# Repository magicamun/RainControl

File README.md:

# RainControl
Füllstandsmessung einer Zisterne, (Über-)steuerung des Schwimmerschalters der Regenwasserpumpe in Abhängigkeit des Füllstands. 
Messung Strom, Verbrauch der Pumpe, Ableitung an/aus. Anbindung an einen MQTT-Broker zur Werteerfassung und Steuerung

Das Projekt basiert auf der Arbeit aus diesem Repo:

https://github.com/Eisbaeeer/Arduino.Ethernet.Zisterne

Der Nano war aber am Limit was den Speicherplatz angeht und selbst kleinste Optimierungen führten zu zu großen Images oder liefen im Betrieb instabil,
daher habe ich das Projekt auf anderer Hardware aufgesetzt. Zugegeben - das ist jetzt deutlich teurer aber macht so auch mehr Spaß (finde ich).
Ich benötige mangels stabilem WLAN im Technikraum Ethernet - daher das Shield.

Hardware:
  [Arduino MKR Zero](https://store.arduino.cc/collections/mkr-family/products/arduino-mkr-zero-i2s-bus-sd-for-sound-music-digital-audio-data) 
  
  [MKR Ethernet-Shield](https://store.arduino.cc/collections/mkr-family/products/arduino-mkr-eth-shield) - Zur Anbindung an eine Hausatomation, bzw. an einen MQTT-Broker (IOBroker)
  
  Pegelsonde zur Messung des Füllstands mittels Druck - Voraussetzung zur korrekten Füllstandsermittlung ist ein Höhensymmetrisches Volumen (aufrecht stehender Zylinder, Quader), Liegende Zylinderformen sind nicht geeignet. Z.B. so eine hier:
  
  [Füllstandssensor Pegelsensor Drucksensor Wasserstandsensor 4-20mA 0-5m DE](https://www.ebay.de/itm/177255784278?chn=ps&_ul=DE&_trkparms=ispr%3D1&amdata=enc%3A10OVVLQ0TSaWD2zqcidwIyQ23&norover=1&mkevt=1&mkrid=707-134425-41852-0&mkcid=2&mkscid=101&itemid=177255784278&targetid=2381626844604&device=c&mktype=pla&googleloc=9113680&poi=&campaignid=21674357977&mkgroupid=167855164998&rlsatarget=pla-2381626844604&abcId=10011854&merchantid=5588616187&gad_source=1&gad_campaignid=21674357977&gbraid=0AAAAAD_G4xa4yudELXTO8UWhM-5WBP-aM&gclid=CjwKCAjwkvbEBhApEiwAKUz6-0uRbySDVDx1-_a3FiXcqrZ4Tvtlft7q06sarqXWDDbmrJJIIFPkExoCPcMQAvD_BwE)
  
  [Stromsensor SCT013 - 5A, 1V](https://www.amazon.de/HUABAN-Nicht-invasiver-Split-Core-Stromwandlersensor/dp/B089FNQ5GX?th=1)

  [Steckernetzteil 24V DC](https://www.conrad.de/de/p/dehner-elektronik-saw-30-240-1000g-steckernetzteil-festspannung-24-v-dc-1000-ma-24-w-1549855.html)

Bauteile für die Schaltung, Platine
  
  Controller
  - [Spannungswandler TSR-1 2433 (Wandlung Eingangsspannung 24V auf 3,3V](https://www.conrad.de/de/p/tracopower-tsr-1-2433-dc-dc-wandler-print-24-v-dc-3-3-v-dc-1-a-75-w-anzahl-ausgaenge-1-x-inhalt-1-st-156671.html) zur Versorgung der Schaltung mit 3,3V
  - [Strom/Spannungswandler](https://de.aliexpress.com/item/1005001604138590.html) zur Wandlung des Stroms der Sonde in Spannung inkl. Kalibrierung von 0-Punkt und Maximum
  - [Relais Finder 36.11 Schaltspannung 3V](https://www.conrad.de/de/p/finder-36-11-9-003-4011-printrelais-3-v-dc-10-a-1-wechsler-1-st-3323202.html)
  - [Steckerleisten 14 polig](https://www.conrad.de/de/p/econ-connect-buchsenleiste-standard-anzahl-reihen-1-polzahl-je-reihe-14-blg1x14-1-st-1492306.html)
  - [Transistor BC337](https://www.conrad.de/de/p/diotec-transistor-bjt-diskret-bc337-25-to-92-anzahl-kanaele-1-npn-155900.html) zur Schaltung von Relais und LED
  - D1 [Diode (1N 4148)](https://www.conrad.de/de/p/diotec-ultraschnelle-si-diode-1n4148-sod-27-75-v-150-ma-162280.html)
  - R1 [1x Widerstand 330 Ohm](https://www.conrad.de/de/p/yageo-cfr25j330rh-cfr-25jt-52-330r-kohleschicht-widerstand-330-axial-bedrahtet-0207-0-25-w-5-1-st-1417730.html)
  - R2, R3 [2x Widerstand 10k Ohm](https://www.conrad.de/de/p/yageo-cfr25j10kh-cfr-25jt-52-10k-kohleschicht-widerstand-10-k-axial-bedrahtet-0207-0-25-w-5-1-st-1417697.html)
  - [10uF Elko](https://www.conrad.de/de/p/frolyt-e-rf3058-elektrolyt-kondensator-radial-bedrahtet-2-5-mm-10-f-16-v-20-o-x-l-5-mm-x-12-mm-1-st-3046377.html)
  - 3 x [Schraubklemmblock 2 polig](https://www.conrad.de/de/p/deca-1216197-schraubklemmblock-1-50-mm-polzahl-3-blau-1-st-1216197.html) (Sonde Zisterne, Spannungsversorgung 24V, Stromsensor SCT 013)
  - 1 x [Schraubklemmblock 3-polig](https://www.conrad.de/de/p/deca-1282826-schraubklemmblock-1-50-mm-polzahl-2-blau-1-st-1282826.html) (Umschaltung Regenwasserpumpe, Übersteuerung Schwimmerschaltung - ACHTUNG - 230V)
  
  Displaypanel
  - R1 [1x Widerstand 390 Ohm](https://www.conrad.de/de/p/yageo-mf0207f390rh-mf0207fte52-390r-metallschicht-widerstand-390-axial-bedrahtet-0207-0-6-w-1-1-st-1417596.html)
  - [LED - Rot, 3mm](https://www.conrad.de/de/p/quadrios-2111o155-led-bedrahtet-rot-rund-3-mm-700-mcd-30-20-ma-2-v-2583896.html)
  - [2 Taster (Reset und Mode)](https://www.conrad.de/de/p/weltron-t604-t604-drucktaster-24-v-dc-0-05-a-1-x-aus-ein-tastend-l-x-b-x-h-6-x-6-x-9-5-mm-1-st-700479.html)
  Display
  - [2,42" 128X64-OLED-Anzeigemodul SPI - 2.42 Zoll OLED Bildschirm kompatibel mit Arduino UNO R3 - Weiße Schrift OLED :](https://www.az-delivery.de/products/oled-2-4-white?variant=44762703986955&utm_source=google&utm_medium=cpc&utm_campaign=16964979024&utm_content=166733588295&utm_term=&gad_source=1&gbraid=0AAAAADBFYGXj7s2C_h3TASz0DupxomgUw&gclid=EAIaIQobChMI-YCAy9LmjAMVH5CDBx0H8zKnEAQYAyABEgLpafD_BwE)

  Zur Verbindung von Controllerplatine mit der Displayplatine:
  
  2 x [Wannenstecker 8polig](https://www.conrad.de/de/p/bkl-electronic-10120552-stiftleiste-ohne-auswurfhebel-rastermass-2-54-mm-polzahl-gesamt-8-anzahl-reihen-2-1-st-741552.html?hk=SEM&WT.mc_id=google_pla&utm_source=google&utm_medium=cpc&utm_campaign=DE+-+PMAX+-+Nonbrand+-+Learning&utm_id=20402606569&gad_source=1&gad_campaignid=20392975386&gbraid=0AAAAAD1-3H7MMs8aUj1DVyRg7EW9yTu3l&gclid=CjwKCAjwkvbEBhApEiwAKUz6--gW1qskdMad7NtT7sFPgiCQdok8dU4I2qlc02XzfEHAeNsRRdUxyhoCCR4QAvD_BwE)
  
  2 x [Pfostensteckverbinder mit Zugentlastung](https://www.conrad.de/de/p/tru-components-1580952-pfosten-steckverbinder-mit-zugentlastung-rastermass-2-54-mm-polzahl-gesamt-8-anzahl-reihen-2-1-1580952.html?hk=SEM&WT.mc_id=google_pla&utm_source=google&utm_medium=cpc&utm_campaign=DE+-+PMAX+-+Nonbrand+-+Learning&utm_id=20402606569&gad_source=1&gad_campaignid=20392975386&gbraid=0AAAAAD1-3H7MMs8aUj1DVyRg7EW9yTu3l&gclid=CjwKCAjwkvbEBhApEiwAKUz6--gW1qskdMad7NtT7sFPgiCQdok8dU4I2qlc02XzfEHAeNsRRdUxyhoCCR4QAvD_BwE)
  
  1 x [Flachbandkabel 8 polig](https://www.conrad.de/de/p/econ-connect-28awg8gr-flachbandkabel-rastermass-1-27-mm-8-x-0-08-mm-grau-30-50-m-1656444.html)

  Sonstiges Material:
  - Bopla Gehäuse](https://www.conrad.de/de/p/bopla-euromas-m-231-02231000-industrie-gehaeuse-160-x-80-x-85-polycarbonat-lichtgrau-ral-7035-1-st-531785.html?hk=SEM&WT.mc_id=google_pla&utm_source=google&utm_medium=cpc&utm_campaign=DE+-+PMAX+-+Nonbrand+-+Learning&utm_id=20402606569&gad_source=1&gad_campaignid=20392975386&gbraid=0AAAAAD1-3H4SrPRlOXxmb1LvpAf_dMIkF&gclid=Cj0KCQjwnovFBhDnARIsAO4V7mCVA2QiVP_xAGgSJM6bk3FJjILpeI0nTC0QpojrSp9-wGSnNphEn0QaArxKEALw_wcB)
  - [Passende Einbaubuchse für das Netzteil](https://www.conrad.de/de/p/cliff-scd-026-niedervolt-steckverbinder-buchse-einbau-vertikal-5-5-mm-2-1-mm-1-st-735640.html)
  - [Einbaubuchse für Klinkenstecker vom SCT013](https://www.conrad.de/de/p/tru-components-718574-klinken-steckverbinder-3-5-mm-buchse-einbau-vertikal-polzahl-3-stereo-schwarz-1-st-1564526.html)
    
Das Platinenlyout wurde mit KiCad in 2 Projekten erstellt - eines für das Display, eines für den Controller.

Funktionsweise technisch:

Füllstandsmessung:
  Die Sonde wird mit 24V betrieben und da bietet sich ein Netzteil handelsüblich an und eine Spannungswandlung (TSR-1 2433) von den 24V DC auf 3,3V für den Rest der Schaltung (Arduino MKR Zero, Relais, Display).
  Die Sonde liefert einen Strom in Abhängigkeit vom Druck (Füllstandshöhe). Der Wandler macht aus dem Strom eine Ausgangsspannung von 0 bis Vmax (3,3V).
  Diese Spannung wird am A0 (AnalogInput 0) des Arduino erfasst und in einen Füllstand umgerechnet - der Füllstand (Volumen) ist proportional zum gemessenen Wert an A0.
  Voraussetzung ist ein Behälter, dessen Füllstand (Volumen) sich linear proportional zum Druck verhält (Senkrechter Zylinder).
  
  Der Wandler für den Messwert an A0 muss vor Inbetriebnahme des Systems kalibiriert werden.
  ACHTUNG: Die Kalibrierung muss im ersten Schritt grob ohne angeschlossenen Arduino erfolgen um Beschädigungen durch Überspannung am Eingang des Arduino zu vermeiden.
  -> Siehe Kalibrierung und Inbetriebnahme.
  
  In Abhängigkeit von der gemessenen Füllhöhe und zwei einzustellenden Werten (LimitLow, LimitHigh) schaltet der Arduino das Relais sowie eine LED über PIN D14 an oder aus.
  Damit bei unterem Schwellwert / Minimum nicht sofort bei erneutem überschreiten (Nachlauf Regen) wieder zurück geschaltet wird, gibt es einen weiteren Wert (Oberer Schwellwert),
  der erreicht werden muss, damkt zurück auf Zisterne geschaltet wird.

Strom, Pumpe an oder aus:
  Über den Stromsensor SCT013 kann der Zustand der Pumpe (Regenwassernutzung) abgefragt werden, ohne in die Anlage eingreifen zu müssen.
  Dazu wird der Stromsensor unter der Beachtung der Stromflussrichtung um die Phase (nur die Phase) zur Pumpe gelegt.
  Am Ausgang des Sensors wird über Induktion eine Wechselspannung abgegeben. Dabei sind die Werte des Sensors zur korrekten Berechnung des Stroms und der Leistung in der Software einzustellen.
   Wichtig ist eine korrekte Dimensionierung des Sensors - es gibt unterschiedliche Typen. Für eine möglichst feine Auflösung ist der Messbereich (Ampere) des Sensors möglichst klein zu wählen, 
   aber groß genug, dass bei Vollast der Pumpe der Wert der Leistung ausreicht. Der hier benutzte Sensor misst bis 5A -> 1,1kw. Meine Pumpe hat 800 Watt Leistungsaufnahme.
   Gleichzeitig soll der Sensor möglichst große Spannungswerte am Ausgang produzieren, damit die Auflösung des Wertes möglichst fein/genau ist.
   Es gibt die Sensoren mit 0,33V und 1V Ausgangsspannung -> ich nutze hier 1V. Da die Spannung eine Wechselspannung ist, wird über den Spannungsteiler am Sensor die Wechselspannung um +1,65V angehoben.
   Der analoge Wert an A1 wird in einen Wert für den Stromverbrauch umgerechnt. Dazu ist es wichtig, den Messbereich des Sensors, die Ausgangsspannung des Sensors und den Referenzwert am Arduino (Zero 3,3V)
   zu kennen und in der Software einzustellen.

Am Pin D13 ist ein Taster von der Displayplatine angeschlossen, mit dem der Betriebsmodus der Steuerung manuell gesetzt werden kann:
  - Auto - Der Arduino übernimmt die Ventilsteuerung (Relais und Ansteuerung Schwimmerschalter der Pumpe) in abhängigkeit des Füllstandes
  -   Füllstand < LimitLow -> Relais auf "Hauswasser"
  -   Füllstand > LimitHigh -> Relais auf "Zisterne"
  -   Wenn der Füllstand kleiner als LimitLow war und immernoch kleiner als LimitHigh ist -> Ventil auf Hauswasser
  - Manuell Zisterne -> Relais auf "Zisterne"
  - Manuell Hauswasser -> Relais auf "Hauswasser"

  Per Tasterdruck wird zyklisch durch die Betriuebsmodi geschaltet, wobei die tatsächliche Umschaltung erst nach 10Sekunden ohne erneute Tasterbetätigung erfolgt

Das Display zeigt Datum, Uhrzeit, Füllstand und Betriebsmodus an

Mit dem an RST angeschlossenen Taster lässt sich der Controller resetten.

Ventilsteuerung generell:
Der Controller misst den Füllstand und (kann) in Abhängigkeit davon einen Schwimmerschalter für handelsübliche Zisternenpumpen ersetzen. Dazu ist die Steuerung der Pumpe auf "Automatik" zu stellen
und statt des Schwimmerschalters ein 230V - Kabel vom Anschluss des Schwimmerschalters zum Controller (3 - polige Klemme) zu führen.
Am Schraubklemmenblock 3 polig ist in jedem der mittlere Anschluss zu belegen und dann entweder NO (Normally open) oder NC (normally connected) - sonst schaltet am Ventil der Regenwasserpump nichts.

Funktionsweise Software:

Sämtliche Systemzustände werden bei Veränderung alle Sekunde an einen MQTT-Broker gesendet, spätestens alle 30 Sekunden auch unverändert. Das System führt folgende Werte:

- Booted     -> Boot-Zeitpunkt
- Timestamp  (Datum, Uhrzeit)
- Uptime     -> Zeit seit l. Boot/Neustart
- Mode       (0 = Zisterne, 1 = Hauswasser, 2 = Auto) -> Betriebsmodus
- Modus      -> Modus als Text
- Valve      (0 = Zisterne, 1 = Hauswasser) -> Ventilstellung
- Ventil     -> Ventilstellung als Text ("Zisterne", "Hauswasser")
- Reason     -> Grund für Ventilstellung (0 = "Manuell", 1 = "Zisterne voll", 2 = "Zisterne leer")
- Reasontext -> Reason als Text
- AnalogMin  -> Mindestwert, den die Sonde liefern muss, damit Sonde als vorhanden erkannt wird
- AnalogMax  -> Maximaler analoger Wert an A0 für volle Zisterne
- Analog     (0-1023) -> Analoger Messwert der Pegelsonde (0-1023)
- Liter      -> Füllung in Liter
- Prozent    -> Füllstand in %
- LimitLow   -> Unterer Schwellwert in Liter
- LimitHigh  -> Oberer Schwellwert in Liter
- LiterMin   -> Restfüllstand bei "leer" - unterer Grenzwert -> AnalogMin.
- LiterMax   -> maximales Füllvolumen wird benötigt zur Umrechnung des analogen Wertes in Liter (Analog = LiterMax / AnalogMax)
- StatusSonde-> Ist eine Sonde korrekt angeschlosen (Wenn der Analoge Wert unter einem Minimum liegt, dann ist davon auszugehen, dass die Sonde nicht korrekt angeschlossen ist
- HyaRain    -> Pumpe läuft (ON), oder nicht (OFF)
- Current    -> Stromverbrauch in Ampere
- Power      -> Watt (Volt * Leistung pro Sekunde
- KWh        -> KLilowattstunden

Es gilt:
LiterMin <= LimitLow <= LimitHigh <= LiterMax
Bei mir mit 6500l Zisterne und Restmenge von knapp 500l: 
LiterMin = 500, LimitLow = 600, LimitHigh = 1000, LiterMax = 6500. Bei unterschreiten von 600l schaltet das Relais auf Hauswassernachspeisung,
sobald wieder mehr als 1000l in der Zisterne sind, wird zurück auf Zisterne geschaltet.

Per MQTT kann der Controller aber auch gesteuert werden:
 - cmd/Mode [0,1,2,Hauswasser,Zisterne,Auto] -> Es kann der Modus umgestellt werden (nicht nur per Taster)
 - cmd/Limit [low|high]=<Number> -> Einstellen der Schwellwerte 
 - cmd/Calibrate [analogmin|analogmax|litermax]=<number> -> Einstellen der Kalibrierung in der Software nach dem die Sonde und der Wandler kalibriert wurden

Bei eingelegter SD-Card werden die Daten über einen Reset hinaus auf der SD-Card gespeichert und nach Neustart gelesen.
Wenn man darauf verzichtet die Werte nach dem Aufspielen der Software und der Einstellung in der Software zu verändern ist eine SD-Card nicht nötig

Aufbau, Inbetriebnahme
1. Platinenlayout, Produktion der Platinen
  Im Repository sind in den Unterordnern Controller und Displaypanel je ein KiCad-Projekt mit dem Schema und dem Platinenlayout - wer mag, kann damit andere Platinenformate erzeugen
  oder aber die Schaltung anpassen.
  Die zwei Zip-Archive im Hauptverzeichnis enthalten die Gerberdateien um PCB's produzieren zu lassen. [JLCPCB](https://jlcpcb.com) hat mir gute Dienste geleistet. Der Preis für jeweils 5 Stück (kleinste Einheit) Controler und 
  Display liegt bei 13.50$US - zzgl Versand, Zoll ist man dann bei knapp 30$. Lieferzeit etwa 1 Woche (je nach Zollabfertigung und lokalem Shipment)

2. Aufbau der Platine
  Die Platinen mit den Bauteilen bestücken. Dabei mit den flachen anfangen (Widerstände, Diode, Transistor), dann Buchsenleisten, Schraubklemmenblöcke, Relais, Spannungswandler

  Nach dem Zusammenbau, der Bestückung der Platine erfolgt schrittweise die Inbetriebnahme - noch ohne Arduino und ohne den Strom/Spannungswandler.
  Buchsenleisten sind nützlich für den Arduino (quasi ein muss) und für den Strom-/Spannungswandler. 
  Den Strom/Spannungswandler befreie ich von den Schraubklemmen (auslöten) und ersetze die durch Stiftleisten - einfacher Tausch.
  Dazu bekommt die Platine je Gegenstück eine Buchsenleiste 2 polig und 3 polig mit 5er Raster.

  Bei der Displayplatine darauf achten, dass der Wannenstecker auf die Rückseite kommt und die Polung korrekt ist - siehe Bilder

3. Prüfung der Spannungen
   An Pin 3 des Strom/Spannungswandlers müssen 24V anliegen (auf dem Board rechte Buchsenleiste oberer Pin/Buchse)
   Am Schraubklemmenblock für die Sonde müssen 24V anliegen
   Am Pin 3 der Stiftleiste für den Arduino müssen gegenüber GND (Pin 4) 3,3Volt anliegen

3. Einstellen des Strom/Spannungswandlers (idealerweise bei voller Zisterne)
   Erster Durchgang des Einstellens OHNE Arduino
      Zum Einstellen des Stromspannungswandlers wird selbiger in die Buchsenleisten gesteckt. Ebenso wird an der Stiftleiste "Probe" ein Multimeter zur Spannungsmessung angeschlossen.
      Ohne Sonde liefert das Multimeter dann 0V. Dann wird die Sonde angeschlossen und noch nicht in die Zisterne herabgelasse. Es erfolgt die Nullpunkteinstellung für "leer".
      Mit dem linken Poti dreht man jetzt solange nach links (kleiner) oder nach rechts (größer), bis die gemessene Spannung verlässlich nah an 0V liegt aber eben noch größer als 0V ist.
      Jetzt kann die Sonde in die Zisterne gelassen werden - so tief wie möglich. Zur korrekten Kalibrierung des Maximalwertes ist es am einfachsten den maximalen Füllstand auch zur Einstellung
      der maximalen Spannung zu nutzen. Dazu dreht man jetzt am rechten Poti des Wandlers (links kleiner, rechts größer) bis die gemessene Spannung nah bei 3,3V ist. Es empfiehlt sich etwas "Luft" zu lassen.
   Zweiter Durchgang mit Arduino - die Werte sind verändert, die Vorgehensweise ist die gleiche
      Wichtig ist jetzt, dass jetzt die Analogen Messwerte angeschaut werden.
      Messwert 1 "Sonde angeschlossen, aber nicht unter Druck" -> Dies wird mit dem Poti links auf einen möglichst kleinen aber stabil kleinen Wert über Null eingestellt (bei mir 50).
      Dieser Wert wird in der Software im #DEFINE ANALOG_MIN abgelegt.
      Messwert 2 "Sonde angeschlossen und Maximaler Füllstand der Zisterne und Sonde am tiefsten Punkt (maximaler Druck)
      Den Messwert stellen wir mit dem rechten Poti so ein, dass er möglichst groß ist (nah an 1023), aber noch etwas Luft ist, falls die Zisterne mal "übervoll" ist - Mehr Zulauf als Ablauf (kommt schonmal vor bei mir)
      Den Wert dann in #DEFINE ANALOG_MAX ablegen.
      Die Defines für LITER_MIN mit einem Wert für die Restmenge in der Zisterne bevor die Pumpe auf Störung laufen würde (bei mir sind dann noch 15cm in der Zisterne drin und damit rund 470 Liter.
      LITER_MAX einstellen mit dem maximalen regulären Füllvolumen der Zisterne.

   Wenn die Zisterne nicht voll ist, sollte man abschätzen können, wie voll (in Prozent) sie ist, man kann dann ausgehend vom Zielwert bei "Zisterne Voll" nah bei 3,3V und
   dem unteren Messwert für "leer" den Spannungswert, den man jetzt messen möchte im Dreisatz ableiten und dann einstellen am Poti.
4. Aufspielen der Software auf den Arduino
5. Board stromlos machen / Spannungsversorgung trennen
6. Aufstecken des Arduino und des Ethernet-Shields auf die Buchsenleisten 14 polig
7. Verbinden des Displays mit dem Controller (Wenn das Display NICHT angeschlossen ist, dann wird der Arduino NICHTS tun.)
8. Netzteil anschließen
9. Der Arduino bootet und auf dem Display werden die Daten angezeigt
10. Die Daten werden zyklisch an den MQTT-Broker verteilt (Bei Änderungen sekündlich, ansonsten alle 30 Sekunden)
11. Prüfung der Messwerte am Broker
12. Es empfiehlt sich, dass nach ein paar Wochen Betrieb und Leer, Voll-Zyklen nochmal die Messwerte der Kalibrierung geprüft werden und notfalls nochmal in der Software neu eingestellt werden - entweder per MQTT oder "hart" per Software

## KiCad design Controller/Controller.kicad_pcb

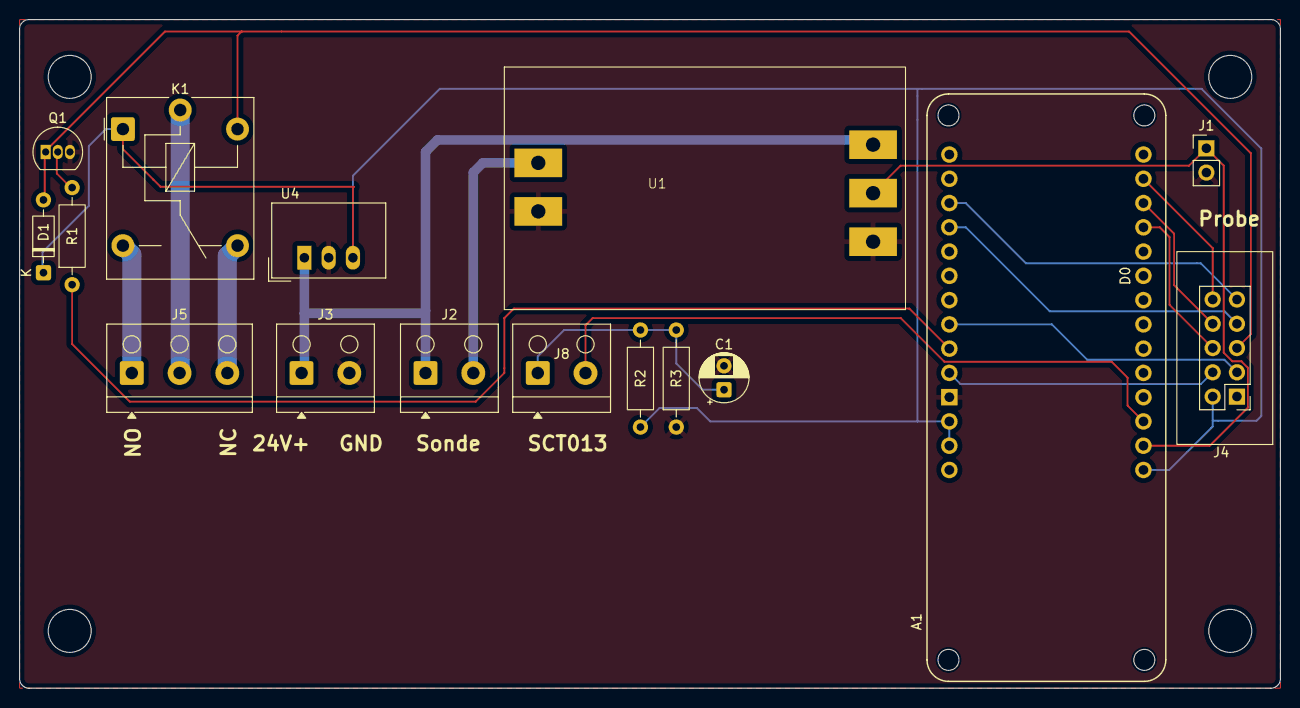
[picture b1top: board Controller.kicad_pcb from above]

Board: 2 copper layers, 132.0 x 70.0 mm, 16 parts (0 on the bottom side), 20 nets.

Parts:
A1: Arduino_MKR_Zero_Socket
C1: 10uF; CP_Radial_D5.0mm_P2.50mm
D1: 1N4148; D_DO-35_SOD27_P7.62mm_Horizontal
J1: Probe; PinHeader_1x02_P2.54mm_Vertical
J2: Sonde; TerminalBlock_RND_205-00001_1x02_P5.00mm_Horizontal
J3: Power; TerminalBlock_RND_205-00001_1x02_P5.00mm_Horizontal
J4: D_Connector; WSL 10G
J5: HayRain 3 Way; TerminalBlock_RND_205-00002_1x03_P5.00mm_Horizontal
J8: SCT013; TerminalBlock_RND_205-00001_1x02_P5.00mm_Horizontal
K1: FINDER-36.11; Relay_SPDT_Finder_36.11
Q1: BC337; TO-92_Inline
R1: 330; R_Axial_DIN0207_L6.3mm_D2.5mm_P10.16mm_Horizontal
R2, R3: 10k; R_Axial_DIN0207_L6.3mm_D2.5mm_P10.16mm_Horizontal
U1: Konverter
U4: TSR_1-2433; Converter_DCDC_TRACO_TSR-1_THT

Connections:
/Hauswasser: J5.1, K1.14
/K: A1.A1, J8.2
/L: C1.1, J8.1, R2.1, R3.2
/Sonde Output: J2.2, U1.1 (+)
/Ventil: J5.2, K1.11
/Zisterne: J5.3, K1.12
CS: A1.D2, J4.6
DC: A1.D3, J4.8
GND: A1.GND, C1.2, J1.2, J3.2, J4.1, Q1.3 (E), R3.1, U1.2 (-), U1.5 (GND), U4.2 (GND)
MODE: A1.D13 (D13/RX), J4.3
unnamed: A1.A0 (A0/DAC), J1.1, U1.4 (Vout)
unnamed: Q1.2 (B), R1.2
RST: A1.D4, J4.10
Reset: A1.RST (RESET), J4.4
SCL: A1.D9 (D9_SCK), J4.7
SDA: A1.D8 (D8_MOSI), J4.9
STATE: D1.2 (A), J4.5, K1.A2, Q1.1 (C)
VALVE: A1.D14 (D14/TX), R1.1
VCC: A1.3V3 (3.3V), A1.AREF, A1.VIN, D1.1 (K), J4.2, K1.A1, R2.2, U4.3 (Vout)
VCC24: J2.1, J3.1, U1.3 (VCC), U4.1 (Vin)

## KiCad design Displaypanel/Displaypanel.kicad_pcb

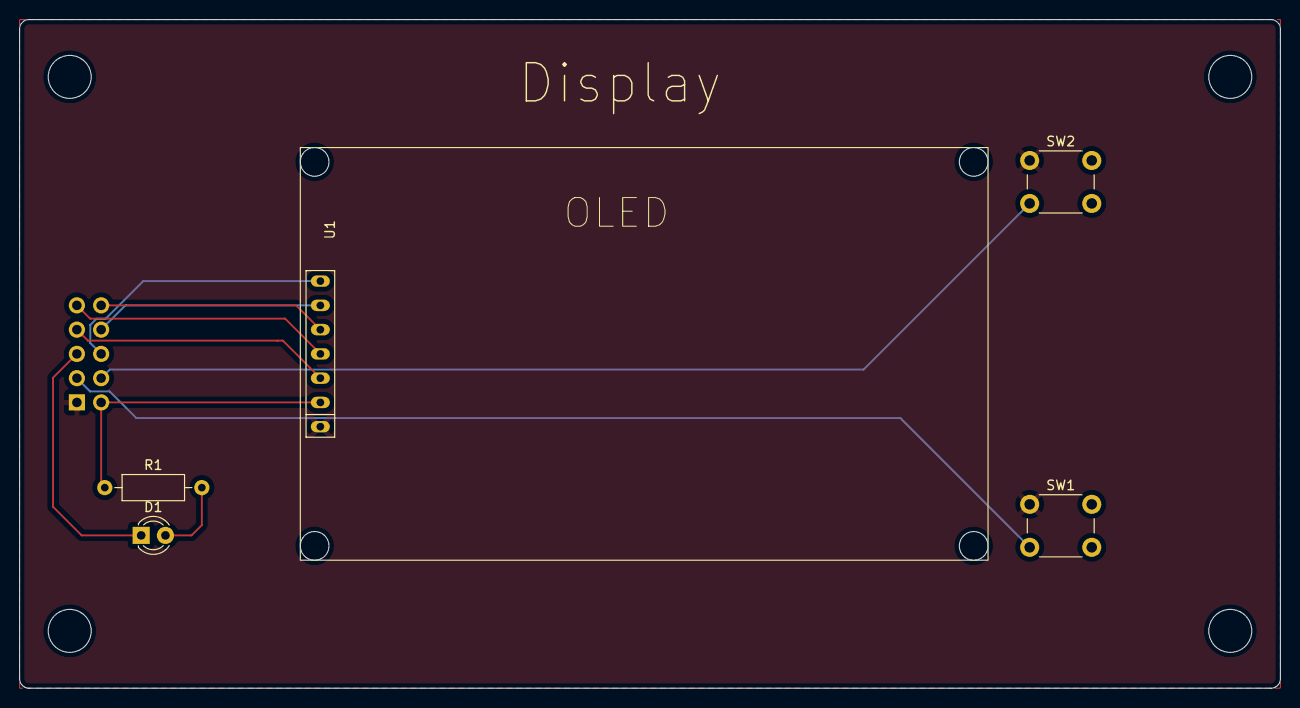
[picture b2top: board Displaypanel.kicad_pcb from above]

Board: 2 copper layers, 132.0 x 70.0 mm, 6 parts (1 on the bottom side), 11 nets.

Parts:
D1: LED; LED_D3.0mm_Clear
J1: D_Connector; WSL 10G
R1: 390; R_Axial_DIN0207_L6.3mm_D2.5mm_P10.16mm_Horizontal
SW1, SW2: SW_Push_Dual; SW_PUSH_6mm_H4.3mm
U1: OLED 128x64 SPI

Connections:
CS: J1.6, U1.7 (CS)
DC: J1.8, U1.6 (DC)
GND: J1.1, SW1.1, SW2.1, U1.1 (GND)
MODE: J1.3, SW1.2
unnamed: D1.2 (A), R1.2
RST: J1.10, U1.5 (RES)
Reset: J1.4, SW2.2
SCL: J1.7, U1.3 (SCL)
SDA: J1.9, U1.4 (SDA)
STATE: D1.1 (K), J1.5
VCC: J1.2, R1.1, U1.2 (VCC)

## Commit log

2025-08-14 Update RainControl.ino
    Removed Commented Code
2025-08-14 Documented, Changing offset to Average
2025-08-14 Changed Picture and Readme
2025-08-14 Picture renamed
2025-08-14 KICad Controller added
2025-08-14 Updated KiCad Controller
2025-08-15 Added DisplayPanel
2025-08-15 Updated Readme (Display)
2025-08-15 Updated KiCad, Gerber-Files
2025-08-15 Added PDF of Displaypanel
2025-08-15 Moved Displaypanel.pdf
2025-08-15 Moved Gerberfiles
2025-08-15 Clean_Up Sketch, Update Readme
2025-08-16 Fixed Output of Topics, Code-Cleanup
2025-08-17 Changed Readme, Bumped Version
    Changed version/Revision to 1.0
    Fixed MQTT_ID
2025-08-21 Bessere Deklaration der Topics
2025-08-24 Fixed Energy
2025-08-28 Update RainControl.ino
    Topics mit Formatierungsoption versehen
2025-08-30 Update RainControl.ino
    Umbau Ausgabe Display
2025-09-03 Update RainControl.ino
    Set Resolution to 12 Bit, Anpassung des Codes - Nutzung ADC_RESOLUTION_BITS etc, Rundung Ampere auf 0,1
2025-09-03 Footprints updated, AREF to VCC
    Updated Footprints from updatet Libraries and connected AREF to VCC,
    Rerouted
2025-09-04 Update RainControl.ino
    Umstellung auf MyNTP-Lib - korrigierte Version für ntp.localTime
